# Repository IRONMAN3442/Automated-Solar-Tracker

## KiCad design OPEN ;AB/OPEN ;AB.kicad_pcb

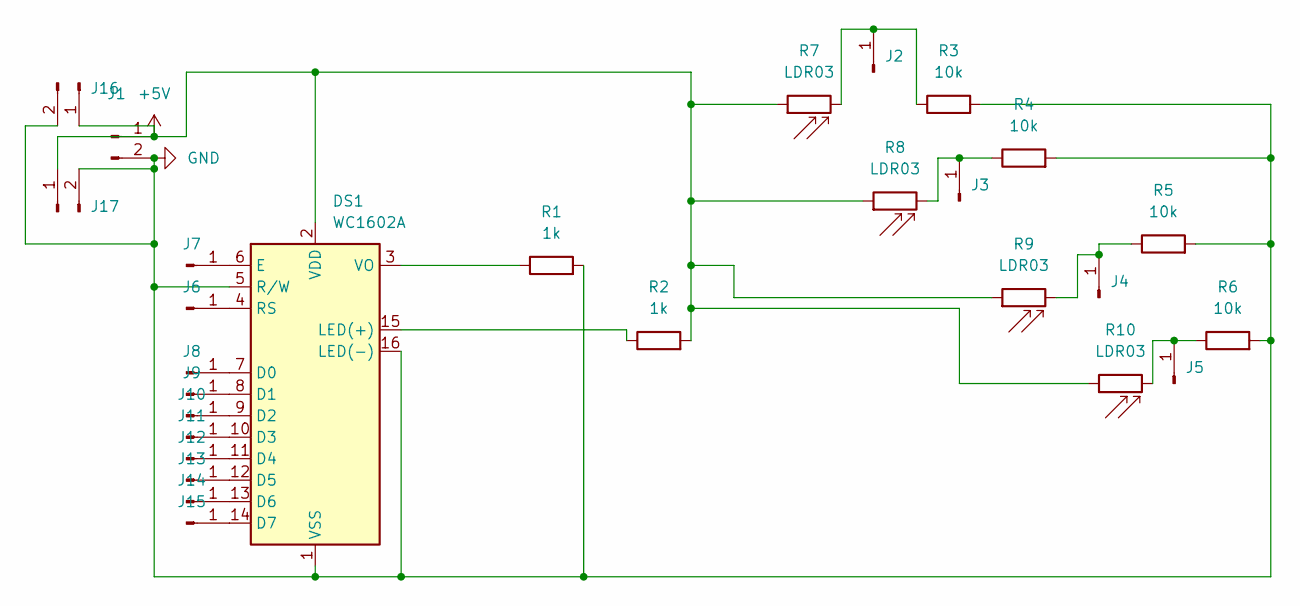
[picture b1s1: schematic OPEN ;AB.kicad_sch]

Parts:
DS1: WC1602A
J1, J16, J17: TestPoint_2Pads_Pitch2.54mm_Drill0.8mm
J2, J3, J4, J5, J6, J7, J8, J9, J10, J11, J12, J13, J14, J15: TestPoint_Loop_D1.80mm_Drill1.0mm_Beaded
R1, R2: 1k; R_Axial_DIN0204_L3.6mm_D1.6mm_P5.08mm_Horizontal
R3, R4, R5, R6: 10k; R_Axial_DIN0204_L3.6mm_D1.6mm_P5.08mm_Horizontal
R7, R8, R9, R10: LDR03; R_LDR_10x8.5mm_P7.6mm_Vertical

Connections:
+5V: DS1.2 (VDD), J1.1, J16.1, J17.1, R2.2, R7.1, R8.1, R9.1, R10.1
GND: DS1.1 (VSS), DS1.5 (R/W), DS1.16 (LED(-)), J1.2, J16.2, J17.2, R1.2, R3.2, R4.2, R5.2, R6.2
unnamed: DS1.7 (D0), J8.1
unnamed: DS1.8 (D1), J9.1
unnamed: DS1.9 (D2), J10.1
unnamed: DS1.10 (D3), J11.1
unnamed: DS1.11 (D4), J12.1
unnamed: DS1.12 (D5), J13.1
unnamed: DS1.13 (D6), J14.1
unnamed: DS1.14 (D7), J15.1
unnamed: DS1.6 (E), J7.1
unnamed: DS1.15 (LED(+)), R2.1
unnamed: DS1.4 (RS), J6.1
unnamed: DS1.3 (VO), R1.1
unnamed: J2.1, R3.1, R7.2
unnamed: J3.1, R4.1, R8.2
unnamed: J4.1, R5.1, R9.2
unnamed: J5.1, R6.1, R10.2

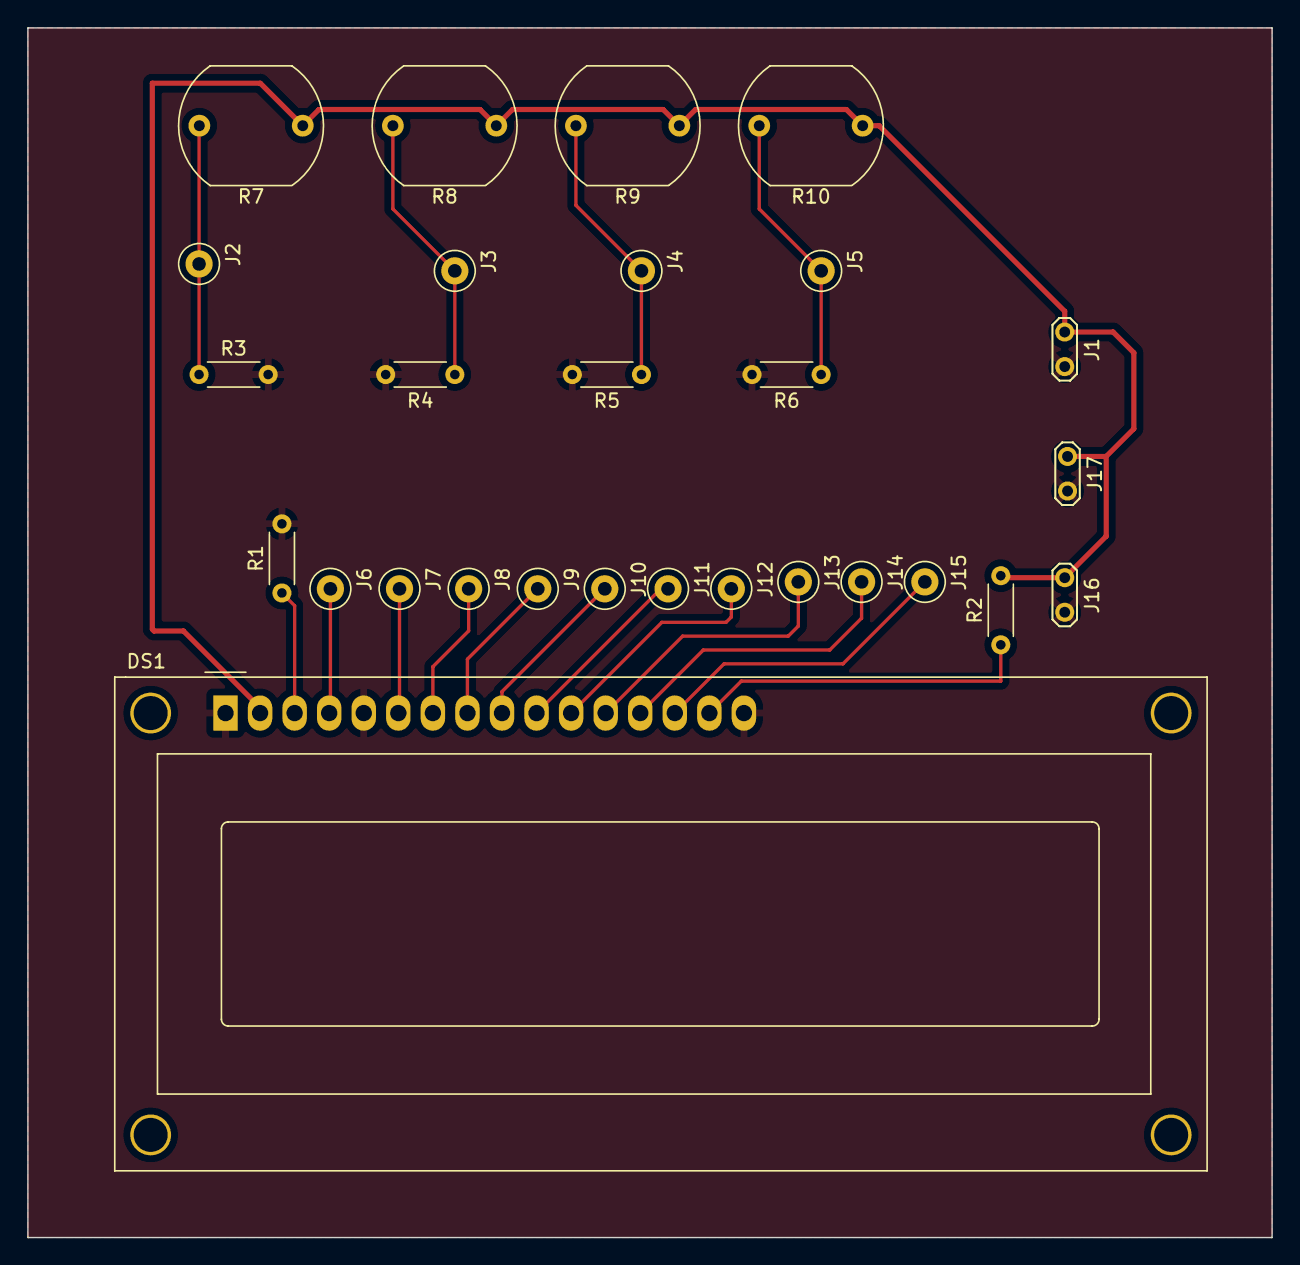
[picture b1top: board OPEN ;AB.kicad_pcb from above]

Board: 2 copper layers, 91.4 x 88.9 mm, 28 parts (0 on the bottom side), 18 nets.
